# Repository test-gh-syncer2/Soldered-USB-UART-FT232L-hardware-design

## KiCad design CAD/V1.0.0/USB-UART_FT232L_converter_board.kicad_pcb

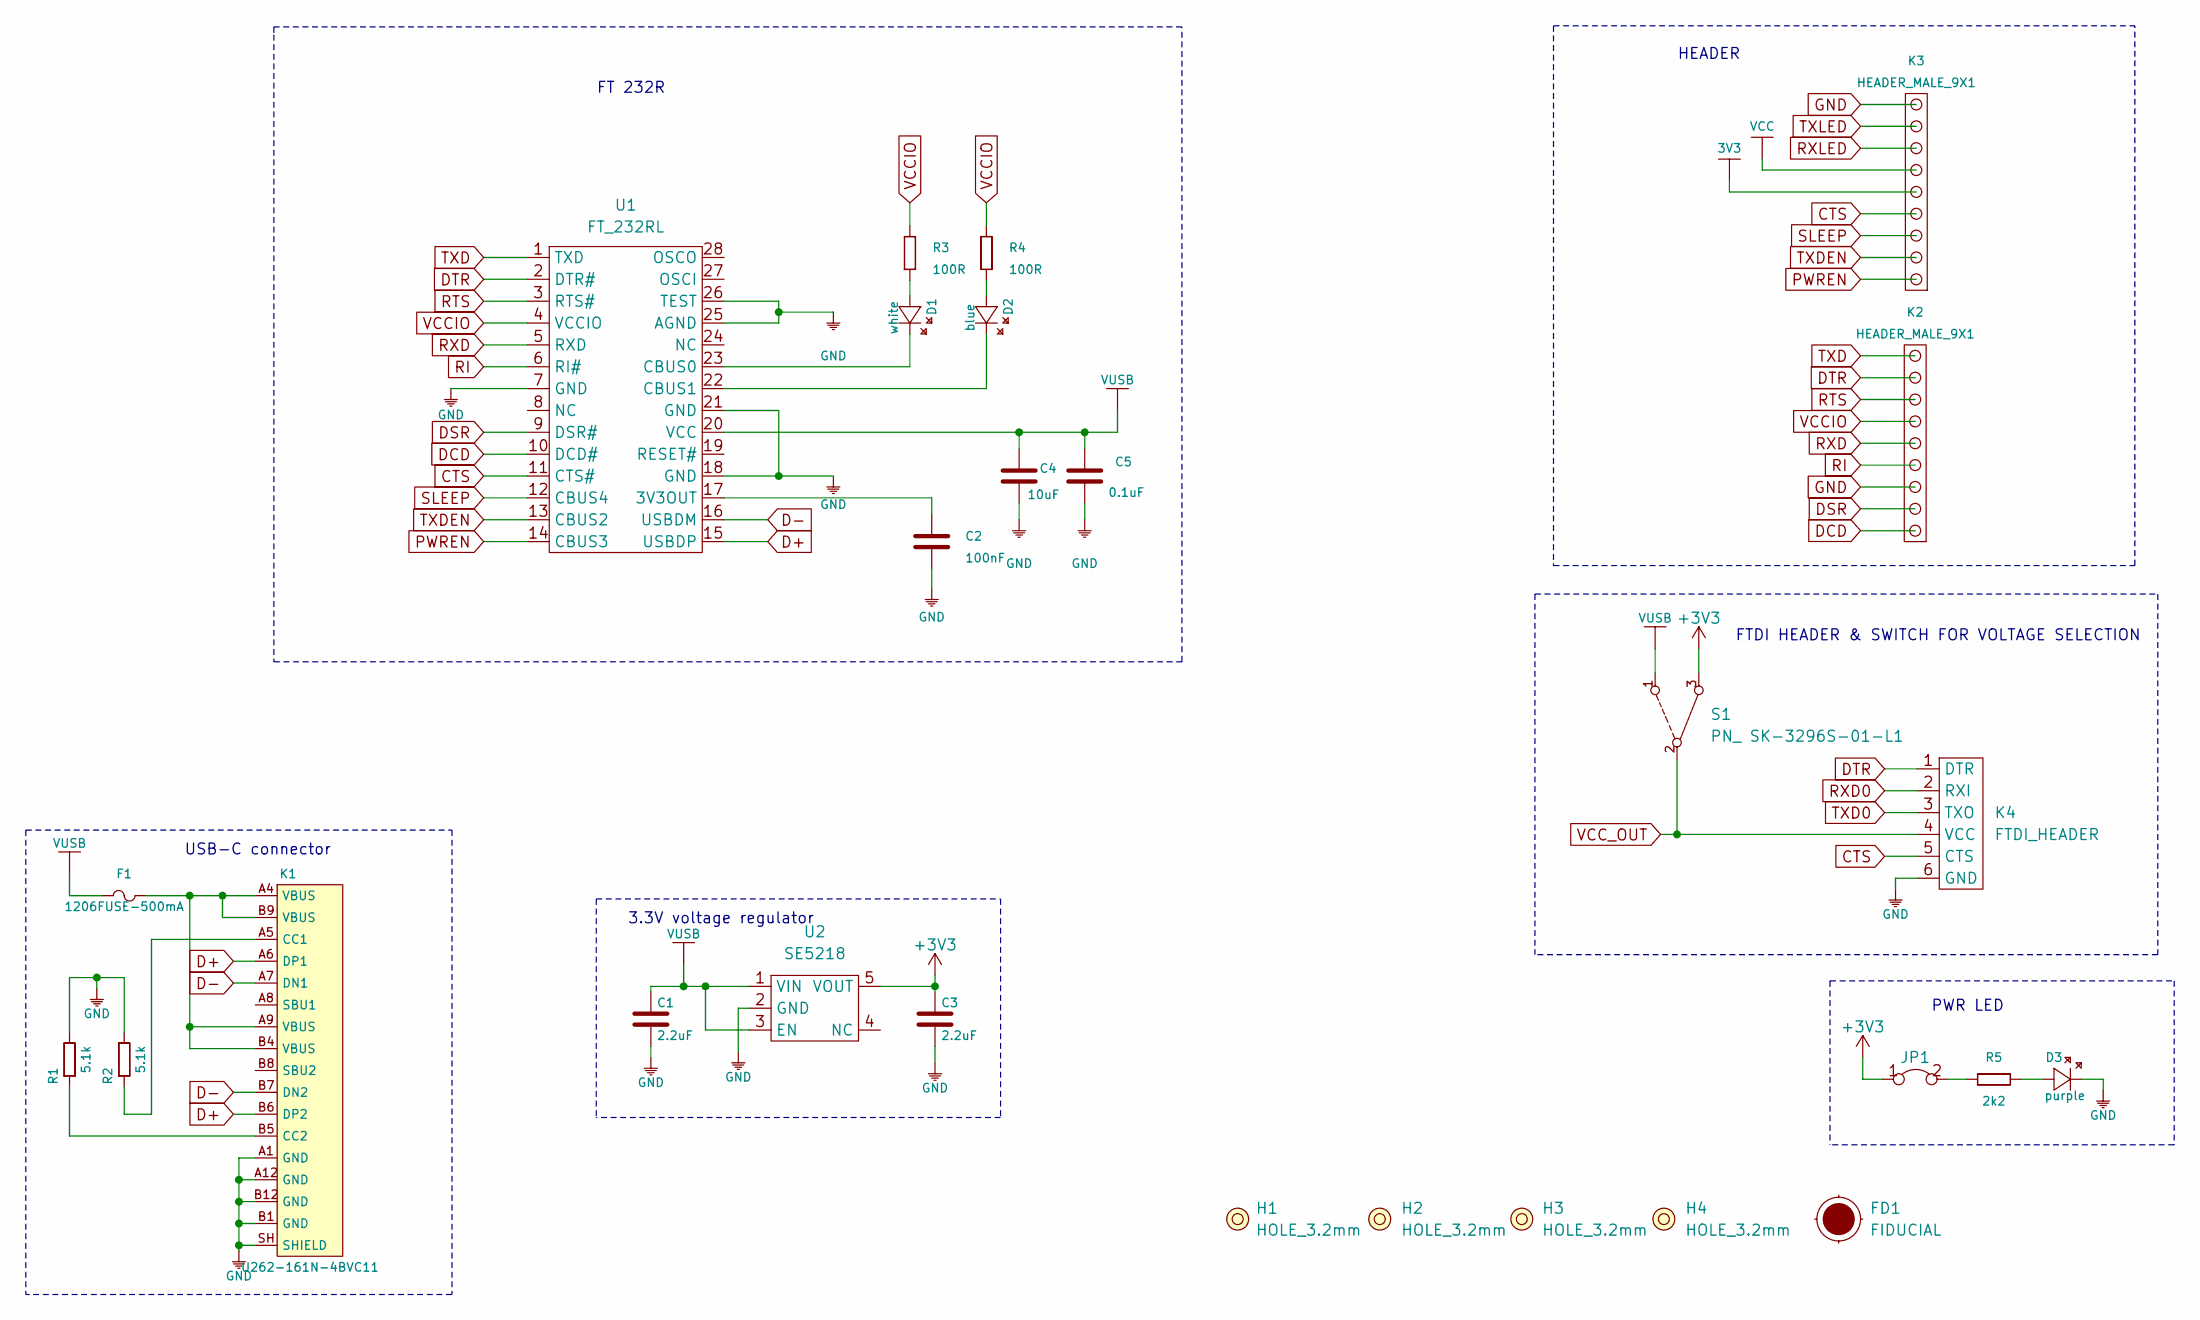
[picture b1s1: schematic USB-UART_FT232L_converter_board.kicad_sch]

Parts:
C1, C3: 2.2uF; 0603C
C2: 100nF; 0603C
C4: 10uF; 1206C
C5: 0.1uF; 0603C
D1: white; 0402LED
D2: blue; 0402LED
D3: purple; 0402LED
F1: 1206FUSE-500mA; 1206FUSE
FD1: FIDUCIAL; FIDUCIAL_23
H1, H2, H3, H4: HOLE_3.2mm
JP1: SMD-JUMPER-CONNECTED_TRACE_SLODERMASK
K1: U262-161N-4BVC11
K2, K3: HEADER_MALE_9X1
K4: FTDI_HEADER; HEADER_MALE_6X1
R1, R2: 5.1k; 0603R
R3, R4: 100R; 0603R
R5: 2k2; 0402R
S1: PN_ SK-3296S-01-L1; SWITCH_ON_OFF_ON_3296
U1: FT_232RL; FT232RL
U2: SE5218; SOT-23-5

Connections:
3V3: K3.5
+3V3: C3.2, JP1.1, S1.3, U2.5 (VOUT)
CTS: K3.4, K4.5 (CTS), U1.11 (CTS#)
D+: K1.A6 (DP1), K1.B6 (DP2), U1.15 (USBDP)
D-: K1.A7 (DN1), K1.B7 (DN2), U1.16 (USBDM)
DCD: K2.1, U1.10 (DCD#)
DSR: K2.2, U1.9 (DSR#)
DTR: K2.8, K4.1 (DTR), U1.2 (DTR#)
GND: C1.1, C2.2, C3.1, C4.1, C5.1, D3.2 (K), K1.A1 (GND), K1.A12 (GND), K1.B1 (GND), K1.B12 (GND), K1.SH (SHIELD), K2.3, K3.9, K4.6 (GND), R1.2, R2.2, U1.7 (GND), U1.18 (GND), U1.21 (GND), U1.25 (AGND), U1.26 (TEST), U2.2 (GND)
unnamed: C2.1, U1.17 (3V3OUT)
unnamed: D1.1 (A), R3.1
unnamed: D1.2 (K), U1.23 (CBUS0)
unnamed: D2.1 (A), R4.1
unnamed: D2.2 (K), U1.22 (CBUS1)
unnamed: D3.1 (A), R5.2
unnamed: F1.2, K1.A4 (VBUS), K1.A9 (VBUS), K1.B4 (VBUS), K1.B9 (VBUS)
unnamed: JP1.2, R5.1
unnamed: K1.A5 (CC1), R2.1
unnamed: K1.B5 (CC2), R1.1
PWREN: K3.1, U1.14 (CBUS3)
RI: K2.4, U1.6 (RI#)
RTS: K2.7, U1.3 (RTS#)
RXD: K2.5, U1.5 (RXD)
RXD0: K4.2 (RXI)
RXLED: K3.7
SLEEP: K3.3, U1.12 (CBUS4)
TXD: K2.9, U1.1 (TXD)
TXD0: K4.3 (TXO)
TXDEN: K3.2, U1.13 (CBUS2)
TXLED: K3.8
VCC: K3.6
VCCIO: K2.6, R3.2, R4.2, U1.4 (VCCIO)
VCC_OUT: K4.4 (VCC), S1.2
VUSB: C1.2, C4.2, C5.2, F1.1, S1.1, U1.20 (VCC), U2.1 (VIN), U2.3 (EN)

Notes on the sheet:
USB-C connector
FT 232R
3.3V voltage regulator
HEADER
PWR LED
FTDI HEADER & SWITCH FOR VOLTAGE SELECTION

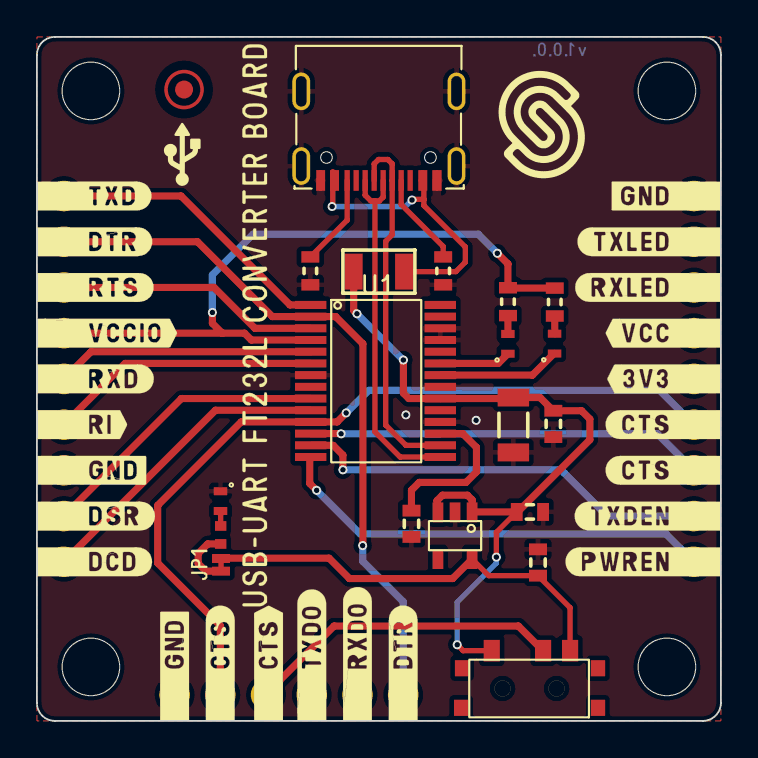
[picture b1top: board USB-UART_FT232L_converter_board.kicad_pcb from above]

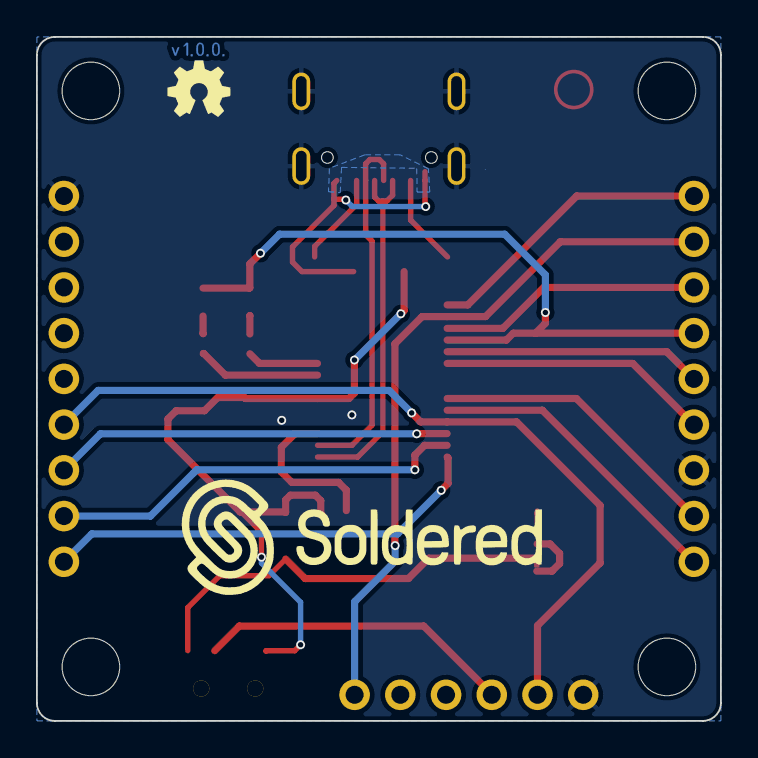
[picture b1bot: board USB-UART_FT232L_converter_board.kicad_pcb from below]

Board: 2 copper layers, 38.0 x 38.0 mm, 28 parts (4 on the bottom side), 28 nets.

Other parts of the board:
Ref**: Val**; Version1.0.0.

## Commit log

2021-09-23 Syncing to git
